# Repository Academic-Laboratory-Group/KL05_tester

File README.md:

# KL05_tester
Project for studies on subject Testing and Reliability.  
[Movie on YouTube](https://youtu.be/P3iQw-8CX4w)

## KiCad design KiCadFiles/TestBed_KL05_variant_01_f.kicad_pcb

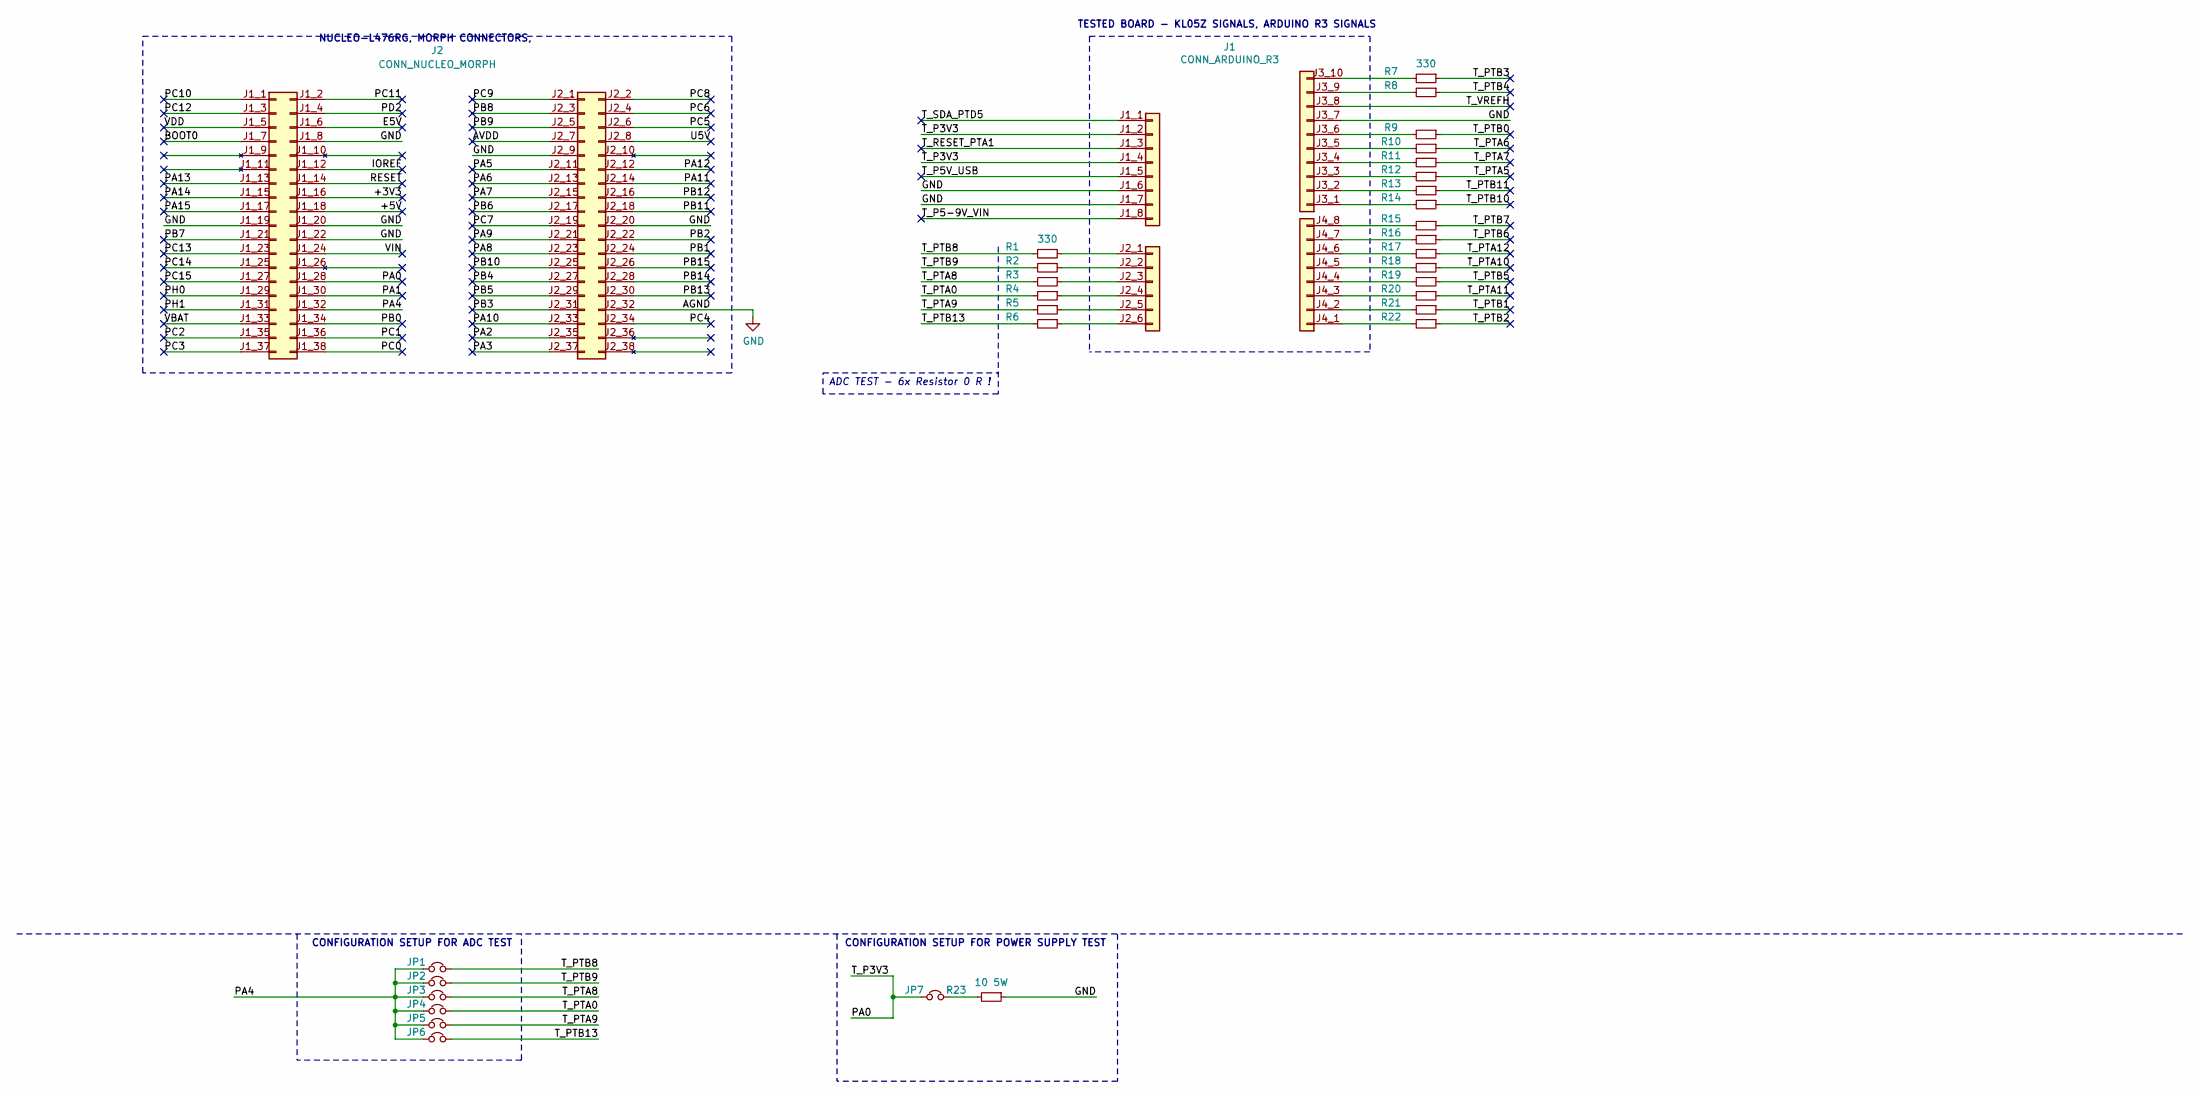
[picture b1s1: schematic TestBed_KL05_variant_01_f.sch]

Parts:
J1: CONN_ARDUINO_R3
J2: CONN_NUCLEO_MORPH; CONN_MORPH_NUCLEO
JP1, JP2, JP3, JP4, JP5, JP6, JP7: Jumper; PinHeader_1x02_P2.54mm_Vertical
R1, R2, R3, R4, R5, R6, R7, R8, R9, R10, R11, R12, R13, R14, R15, R16, R17, R18, R19, R20, R21, R22: 330; R_0805_2012Metric_Pad1.15x1.40mm_HandSolder
R23: 10 5W; R_Axial_DIN0411_L9.9mm_D3.6mm_P12.70mm_Horizontal

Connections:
/+3V3: J2.J1_16
/+5V: J2.J1_18
/AVDD: J2.J2_7
/BOOT0: J2.J1_7
/E5V: J2.J1_6
/IOREF: J2.J1_12
/PA0: J1.J1_2, J1.J1_4, J2.J1_28, JP7.2
/PA1: J2.J1_30
/PA2: J2.J2_35
/PA3: J2.J2_37
/PA4: J2.J1_32, JP1.2, JP2.2, JP3.2, JP4.2, JP5.2, JP6.2
/PA5: J2.J2_11
/PA6: J2.J2_13
/PA7: J2.J2_15
/PA8: J2.J2_23
/PA9: J2.J2_21
/PA10: J2.J2_33
/PA11: J2.J2_14
/PA12: J2.J2_12
/PA13: J2.J1_13
/PA14: J2.J1_15
/PA15: J2.J1_17
/PB0: J2.J1_34
/PB1: J2.J2_24
/PB2: J2.J2_22
/PB3: J2.J2_31
/PB4: J2.J2_27
/PB5: J2.J2_29
/PB6: J2.J2_17
/PB7: J2.J1_21
/PB8: J2.J2_3
/PB9: J2.J2_5
/PB10: J2.J2_25
/PB11: J2.J2_18
/PB12: J2.J2_16
/PB13: J2.J2_30
/PB14: J2.J2_28
/PB15: J2.J2_26
/PC0: J2.J1_38
/PC1: J2.J1_36
/PC2: J2.J1_35
/PC3: J2.J1_37
/PC4: J2.J2_34
/PC5: J2.J2_6
/PC6: J2.J2_4
/PC7: J2.J2_19
/PC8: J2.J2_2
/PC9: J2.J2_1
/PC10: J2.J1_1
/PC11: J2.J1_2
/PC12: J2.J1_3
/PC13: J2.J1_23
/PC14: J2.J1_25
/PC15: J2.J1_27
/PD2: J2.J1_4
/PH0: J2.J1_29
/PH1: J2.J1_31
/RESET: J2.J1_14
/T_P5-9V_VIN: J1.J1_8
/T_P5V_USB: J1.J1_5
/T_PTA0: JP4.1, R4.2
/T_PTA5: R12.1
/T_PTA6: R10.1
/T_PTA7: R11.1
/T_PTA8: JP3.1, R3.2
/T_PTA9: JP5.1, R5.2
/T_PTA10: R18.1
/T_PTA11: R20.1
/T_PTA12: R17.1
/T_PTB0: R9.1
/T_PTB1: R21.1
/T_PTB2: R22.1
/T_PTB3: R7.1
/T_PTB4: R8.1
/T_PTB5: R19.1
/T_PTB6: R16.1
/T_PTB7: R15.1
/T_PTB8: JP1.1, R1.2
/T_PTB9: JP2.1, R2.2
/T_PTB10: R14.1
/T_PTB11: R13.1
/T_PTB13: JP6.1, R6.2
/T_RESET_PTA1: J1.J1_3
/T_SDA_PTD5: J1.J1_1
/T_VREFH: J1.J3_8
/U5V: J2.J2_8
/VBAT: J2.J1_33
/VDD: J2.J1_5
/VIN: J2.J1_24
GND: J1.J1_6, J1.J1_7, J1.J3_7, J2.J1_8, J2.J1_19, J2.J1_20, J2.J1_22, J2.J2_9, J2.J2_20, J2.J2_32, R23.1
unnamed: J1.J2_1, R1.1
unnamed: J1.J2_2, R2.1
unnamed: J1.J2_3, R3.1
unnamed: J1.J2_4, R4.1
unnamed: J1.J2_5, R5.1
unnamed: J1.J2_6, R6.1
unnamed: J1.J3_1, R14.2
unnamed: J1.J3_2, R13.2
unnamed: J1.J3_3, R12.2
unnamed: J1.J3_4, R11.2
unnamed: J1.J3_5, R10.2
unnamed: J1.J3_6, R9.2
unnamed: J1.J3_9, R8.2
unnamed: J1.J3_10, R7.2
unnamed: J1.J4_1, R22.2
unnamed: J1.J4_2, R21.2
unnamed: J1.J4_3, R20.2
unnamed: J1.J4_4, R19.2
unnamed: J1.J4_5, R18.2
unnamed: J1.J4_6, R17.2
unnamed: J1.J4_7, R16.2
unnamed: J1.J4_8, R15.2
unnamed: JP7.1, R23.2

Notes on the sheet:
CONFIGURATION SETUP FOR ADC TEST
NUCLEO-L476RG, MORPH CONNECTORS,
ADC TEST - 6x Resistor 0 R !
TESTED BOARD - KL05Z SIGNALS, ARDUINO R3 SIGNALS
CONFIGURATION SETUP FOR POWER SUPPLY TEST

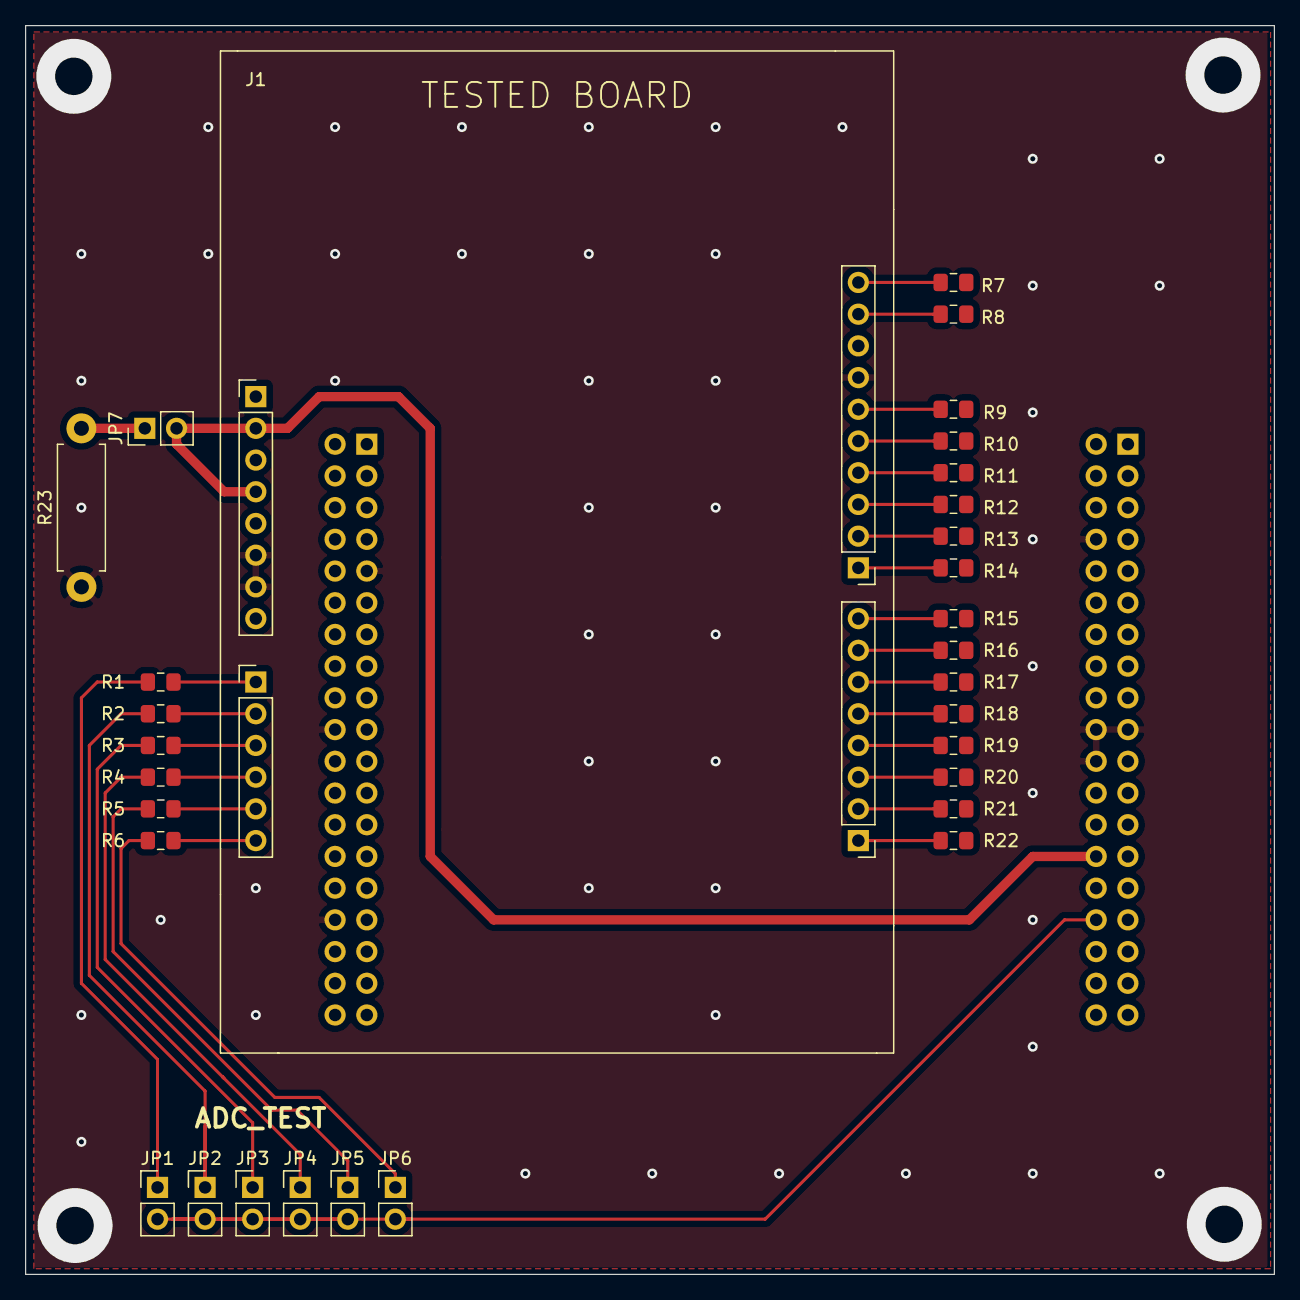
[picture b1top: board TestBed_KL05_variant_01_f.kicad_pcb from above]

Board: 2 copper layers, 100.0 x 100.0 mm, 32 parts (1 on the bottom side), 32 nets.

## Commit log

2021-04-15 initial
2021-04-20 Dokumentacja
2021-04-22 Quick fix
2021-07-25 cleaning up & refresh button & warnings rather than critical error 69
2021-07-25 Refreshing ports
2021-07-25 Problems with connection handled v.1 & and some studpid coder's double language translations fix
2021-07-26 Add first projekt for Power Supply
2021-08-23 Combobox blocks when not needed
2021-08-28 More catching errors, Ready for programing STM
2021-08-28 GUI ready
2021-08-28 typo
2021-08-29 Add nucleo files to NUCLE-F446RE
2021-08-29 update main
2021-08-29 settings with correct hex file placement
2021-08-29 cleaning with gitignore finally
2021-08-29 function not needed anymore
2021-08-29 uart communication
2021-08-29 uart string receive
2021-08-30 Update PCB
2021-08-30 updatecodenucleo
2021-08-30 Done code do platform Nucleo
2021-08-30 right figure and connection and data and show
2021-08-31 Update documentation
2021-08-31 exe with updating script
2021-08-31 legend fixed
2021-09-01 docs to docs, and drive refreshing
2021-09-01 movie
2021-09-02 Add documentation for POWER SUPPY TEST
2021-09-02 presentation
